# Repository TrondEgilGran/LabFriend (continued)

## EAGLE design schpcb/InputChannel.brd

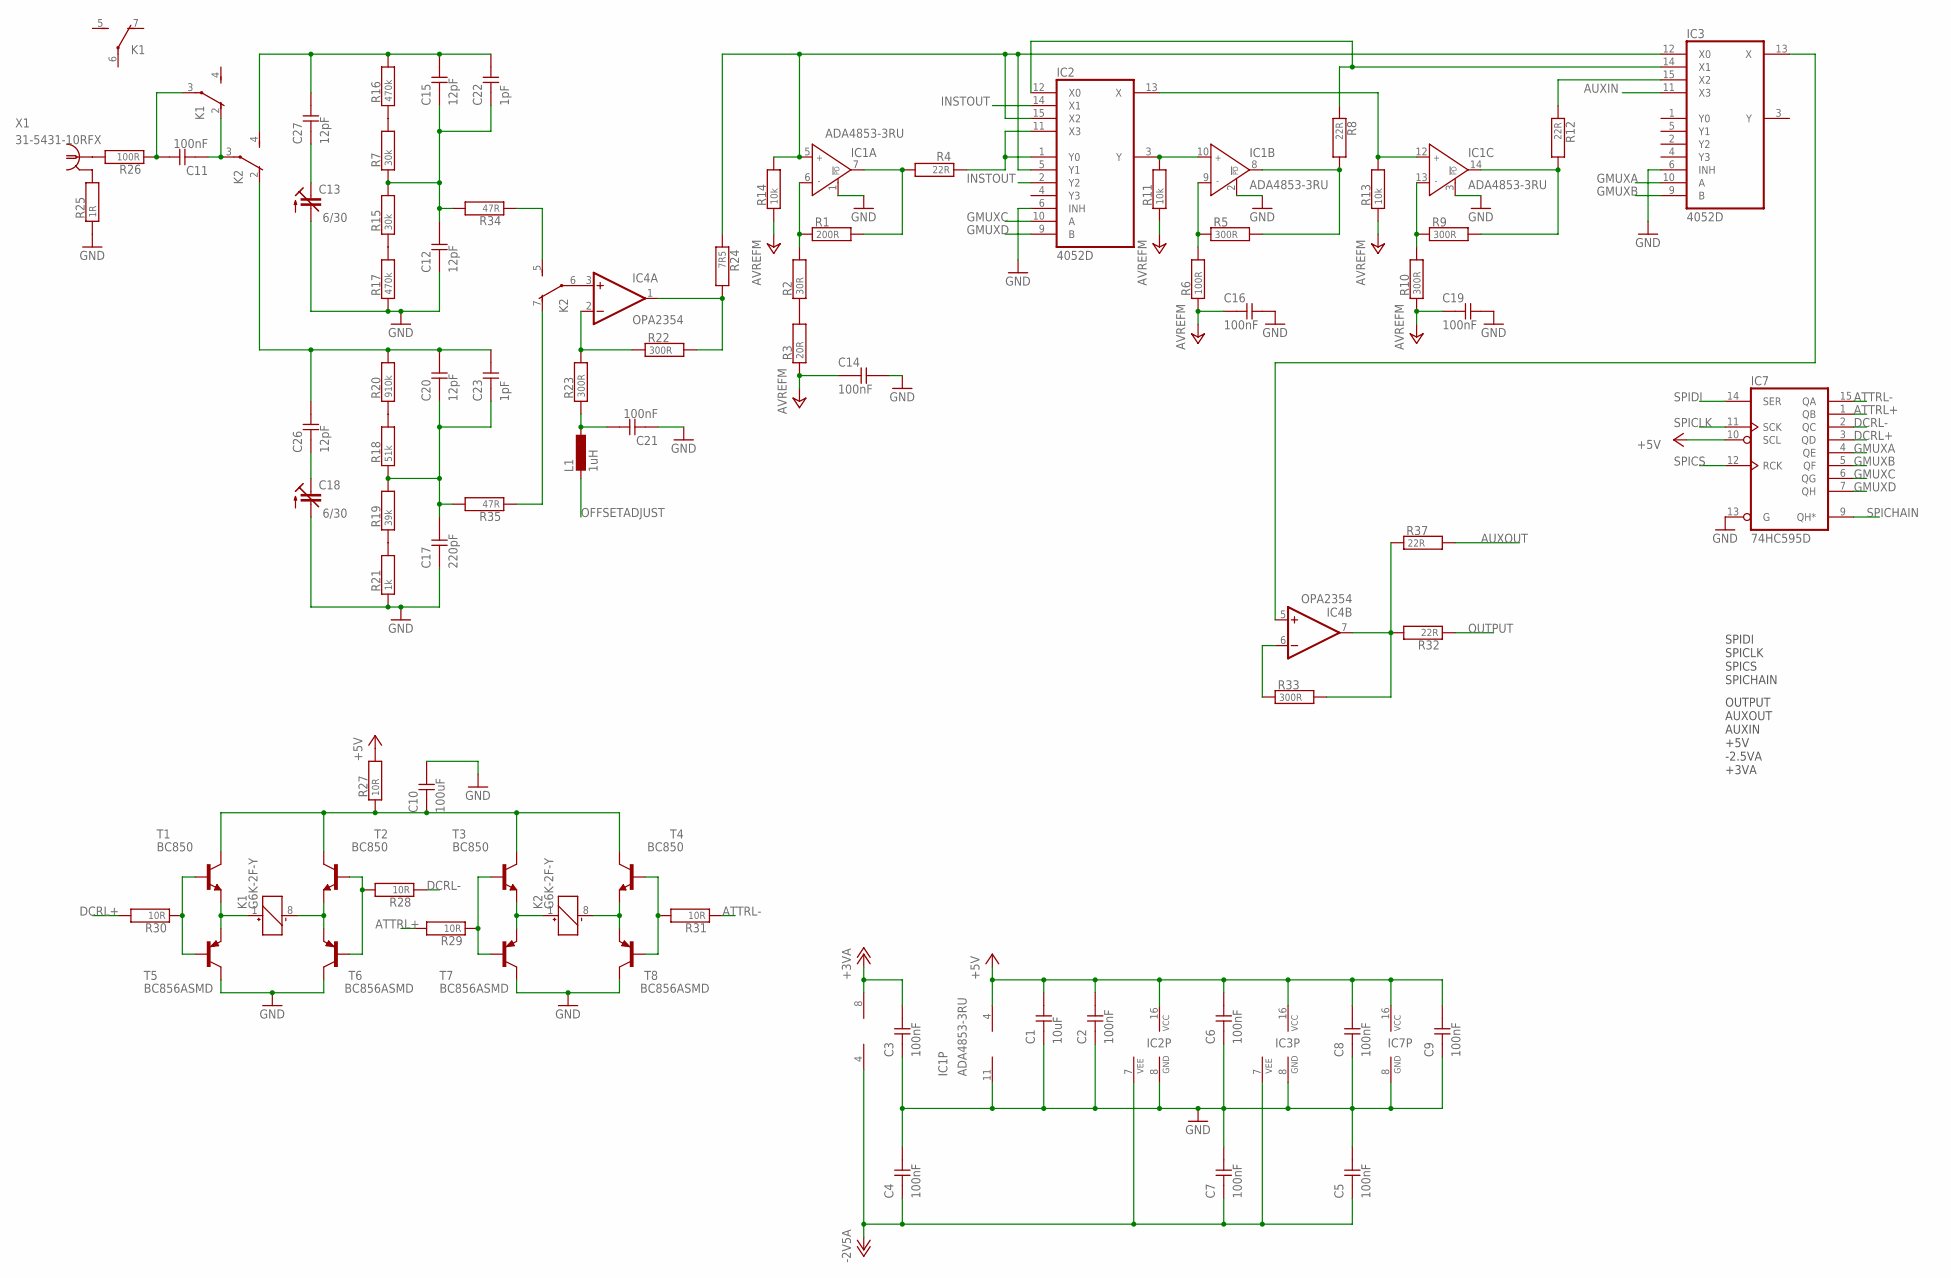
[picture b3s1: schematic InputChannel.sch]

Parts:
C1: 10uF; 0603
C2, C3, C5, C6, C7, C8, C9, C11: 100nF; 0603
C4, C14, C16, C19, C21: 100nF; 0402
C10: 100uF; 1206
C12, C15, C20, C26, C27: 12pF; 0603
C13, C18: 6/30; CTRIMTZBX4
C17: 220pF; 0603
C22, C23: 1pF; 0603
IC1: ADA4853-3RU; SO14
IC2, IC3: 4052D; SO16
IC4: OPA2354; MSOP08
IC7: 74HC595D; SO16
K1, K2: G6K-2F-Y
L1: 1uH; L3216C
R1: 200R; 0603
R2: 30R; 0603
R3: 20R; 0603
R4, R8, R12, R32, R37: 22R; 0603
R5, R9, R10, R22, R23, R33: 300R; 0603
R6, R26: 100R; 0603
R7, R15: 30k; 0603
R11, R13, R14: 10k; 0603
R16, R17: 470k; 0603
R18: 51k; 0603
R19: 39k; 0603
R20: 910k; 0603
R21: 1k; 0603
R24: 7R5; 0603
R25: 1R; 0603
R27, R28, R29, R30, R31: 10R; 0603
R34, R35: 47R; 0603
T1, T2, T3, T4: BC850; SOT23
T5, T6, T7, T8: BC856ASMD; SOT23-BEC
X1: 31-5431-10RFX; AMP_227161

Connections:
+3VA: C3.2, IC4.8 (V+)
+5V: C1.2, C2.2, C6.2, C8.2, C9.2, IC1.4 (V+), IC2.16 (VCC), IC3.16 (VCC), IC7.10 (SCL), IC7.16 (VCC), R27.2
-2V5A: C4.1, C5.1, C7.1, IC2.7 (VEE), IC3.7 (VEE), IC4.4 (V-)
ATTRL+: IC7.1 (QB), R29.2
ATTRL-: IC7.15 (QA), R31.1
AUXIN: IC3.11 (X3)
AUXOUT: R37.2
AVREFM: C14.1, C16.1, C19.1, R3.1, R6.1, R10.1, R11.1, R13.1, R14.1
DCRL+: IC7.3 (QD), R30.2
DCRL-: IC7.2 (QC), R28.1
GMUXA: IC3.10 (A), IC7.4 (QE)
GMUXB: IC3.9 (B), IC7.5 (QF)
GMUXC: IC2.10 (A), IC7.6 (QG)
GMUXD: IC2.9 (B), IC7.7 (QH)
GND: C1.1, C2.1, C3.1, C4.2, C5.2, C6.1, C7.2, C8.1, C9.1, C10.2, C12.1, C13.2 (A), C14.2, C16.2, C17.1, C18.2 (A), C19.2, C21.1, IC1.1 (!POWERDOWN), IC1.2 (!POWERDOWN), IC1.3 (!POWERDOWN), IC1.11 (V-), IC2.6 (INH), IC2.8 (GND), IC3.6 (INH), IC3.8 (GND), IC7.8 (GND), IC7.13 (G), R17.1, R21.1, R25.1, T5.C, T6.C, T7.C, T8.C
INSTOUT: IC2.2 (Y2), IC2.14 (X1)
unnamed: IC1.6 (IN-), R1.1, R2.2
unnamed: IC1.7 (OUT), R1.2, R4.2
unnamed: R2.1, R3.2
unnamed: C11.2, K1.3, R26.1
unnamed: IC1.9 (IN-), R5.1, R6.2
unnamed: IC2.1 (Y0), IC2.11 (X3), R4.1
unnamed: C11.1, K1.2 (O), K2.3
unnamed: IC2.12 (X0), IC3.14 (X1), R8.1
unnamed: IC1.12 (IN+), IC2.13 (X), R13.2
unnamed: IC1.5 (IN+), IC2.5 (Y1), IC2.15 (X2), IC3.12 (X0), R14.2, R24.1
unnamed: R7.2, R16.1
unnamed: IC1.13 (IN-), R9.1, R10.2
unnamed: IC1.14 (OUT), R9.2, R12.2
unnamed: IC3.15 (X2), R12.1
unnamed: IC1.8 (OUT), R5.2, R8.2
unnamed: C12.2, C15.1, C22.1, R7.1, R15.2, R34.2
unnamed: IC1.10 (IN+), IC2.3 (Y), R11.2
unnamed: R18.2, R20.1
unnamed: C17.2, C20.1, C23.1, R18.1, R19.2, R35.2
unnamed: R15.1, R17.2
unnamed: C15.2, C22.2, C27.2, K2.4 (S), R16.2
unnamed: R19.1, R21.2
unnamed: C20.2, C23.2, C26.2, K2.2 (O), R20.2
unnamed: R25.2, X1.2
unnamed: IC4.3 (+IN), K2.6
unnamed: C21.2, L1.1, R23.1
unnamed: IC4.2 (-IN), R22.1, R23.2
unnamed: IC4.1 (OUT), R22.2, R24.2
unnamed: R26.2, X1.1
unnamed: K2.5 (S), R34.1
unnamed: IC3.13 (X), IC4.5 (+IN)
unnamed: C10.1, R27.1, T1.3 (C), T2.3 (C), T3.3 (C), T4.3 (C)
unnamed: IC4.7 (OUT), R32.2, R33.2, R37.1
unnamed: K1.8 (-), T2.2 (E), T6.E
unnamed: K1.1 (+), T1.2 (E), T5.E
unnamed: R30.1, T1.1 (B), T5.B
unnamed: R28.2, T2.1 (B), T6.B
unnamed: K2.1 (+), T3.2 (E), T7.E
unnamed: K2.8 (-), T4.2 (E), T8.E
unnamed: IC4.6 (-IN), R33.1
unnamed: R29.1, T3.1 (B), T7.B
unnamed: R31.2, T4.1 (B), T8.B
unnamed: K2.7 (O), R35.1
unnamed: C18.1 (E), C26.1
unnamed: C13.1 (E), C27.1
OFFSETADJUST: L1.2
OUTPUT: R32.1
SPICHAIN: IC7.9 (QH*)
SPICLK: IC7.11 (SCK)
SPICS: IC7.12 (RCK)
SPIDI: IC7.14 (SER)

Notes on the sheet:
SPIDI SPICLK SPICS SPICHAIN
OUTPUT AUXOUT AUXIN +5V -2.5VA +3VA

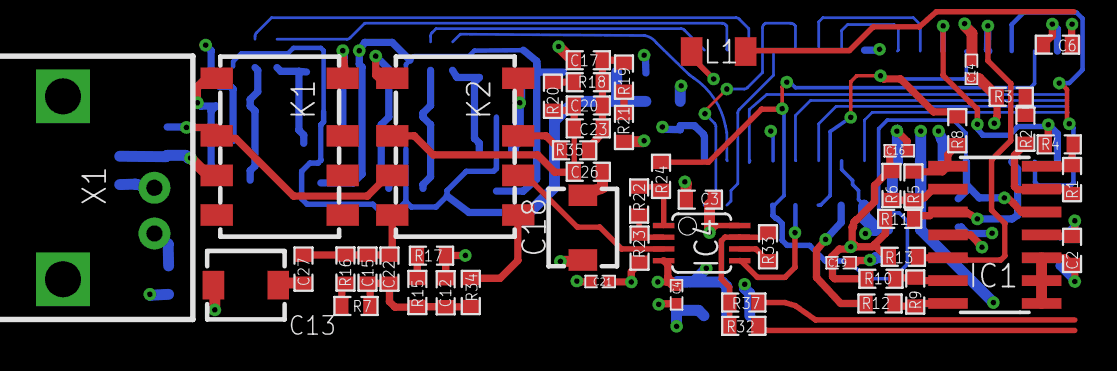
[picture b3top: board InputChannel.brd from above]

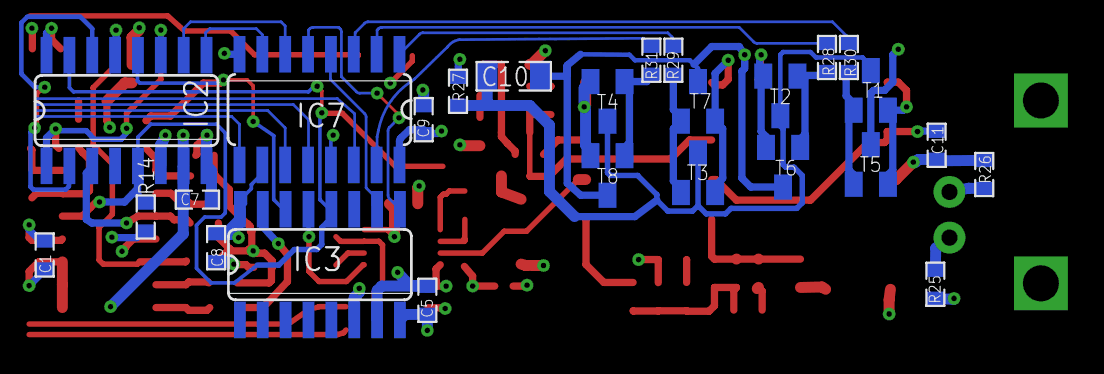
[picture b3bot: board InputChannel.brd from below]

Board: 4 copper layers, 78 parts (26 on the bottom side), 59 nets.

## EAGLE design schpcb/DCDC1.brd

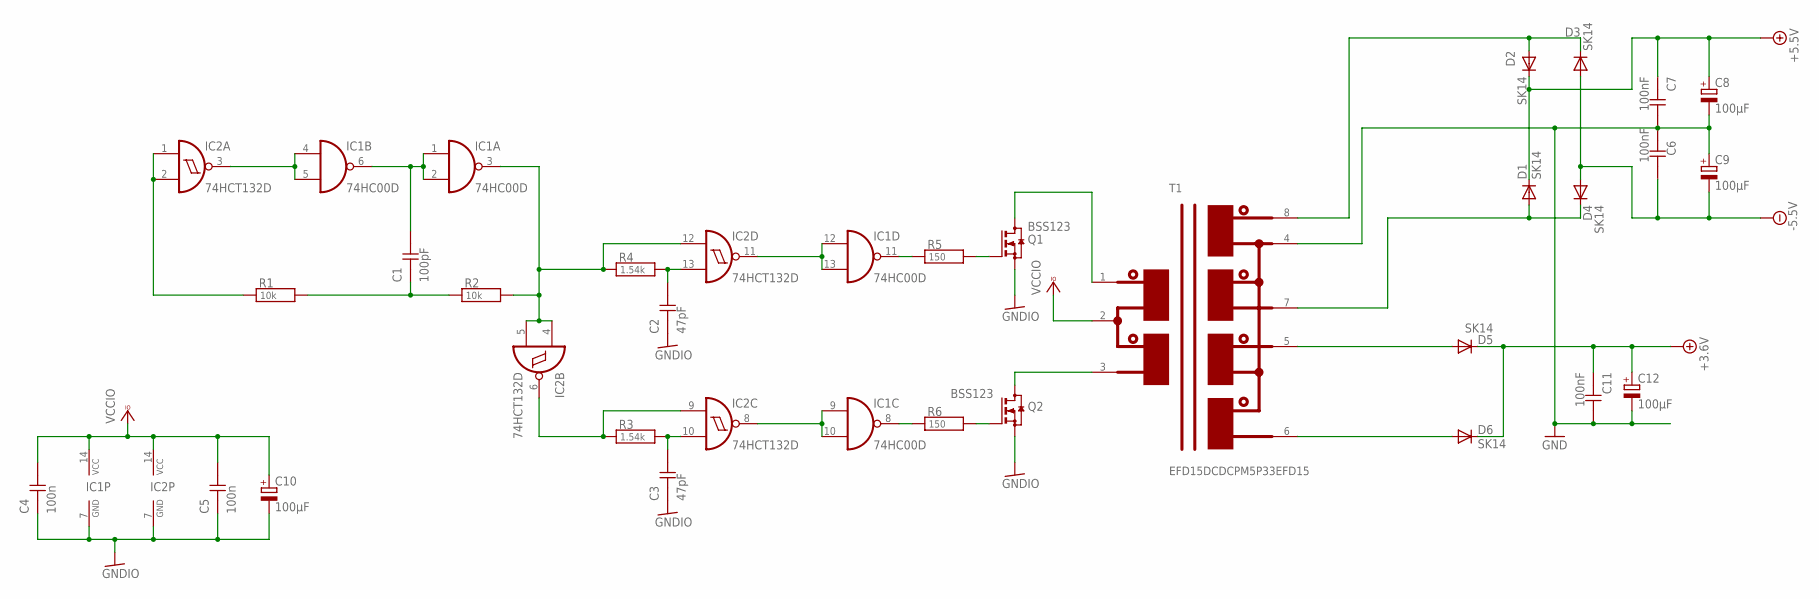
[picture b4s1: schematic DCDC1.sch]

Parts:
C1: 100pF; 0603
C2, C3: 47pF; 0603
C4, C5: 100n; 0603
C6, C7, C11: 100nF; 0603
C8, C9, C10, C12: 100µF; CT6032
D1, D2, D3, D4, D5, D6: SK14; DO214AC
IC1: 74HC00D; SO14
IC2: 74HCT132D; SO14
Q1, Q2: BSS123; SOT23
R1, R2: 10k; 0603
R3, R4: 1.54k; 0603
R5, R6: 150; 0603
T1: EFD15DCDCPM5P33EFD15; B66414-W1008-D1

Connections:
+3.6V: C11.1, C12.+, D5.C, D6.C
+5.5V: C7.1, C8.+, D1.C, D2.C
-5.5V: C6.2, C9.-, D3.A, D4.A
GND: C6.1, C7.2, C8.-, C9.+, C11.2, C12.-, T1.4 (SM)
GNDIO: C2.1, C3.1, C4.1, C5.1, C10.-, IC1.7 (GND), IC2.7 (GND), Q1.2 (S), Q2.2 (S)
unnamed: IC2.1 (I0), IC2.2 (I1), R1.1
unnamed: IC1.4 (I0), IC1.5 (I1), IC2.3 (O)
unnamed: C1.1, R1.2, R2.1
unnamed: C1.2, IC1.1 (I0), IC1.2 (I1), IC1.6 (O)
unnamed: IC1.3 (O), IC2.4 (I0), IC2.5 (I1), IC2.12 (I0), R2.2, R4.1
unnamed: IC1.12 (I0), IC1.13 (I1), IC2.11 (O)
unnamed: C2.2, IC2.13 (I1), R4.2
unnamed: IC2.6 (O), IC2.9 (I0), R3.1
unnamed: C3.2, IC2.10 (I1), R3.2
unnamed: IC1.9 (I0), IC1.10 (I1), IC2.8 (O)
unnamed: IC1.11 (O), R5.1
unnamed: IC1.8 (O), R6.1
unnamed: Q2.1 (G), R6.2
unnamed: D5.A, T1.5 (S2P)
unnamed: Q1.1 (G), R5.2
unnamed: Q1.3 (D), T1.1 (P1P)
unnamed: D1.A, D4.C, T1.7 (S1N)
unnamed: D2.A, D3.C, T1.8 (S1P)
unnamed: Q2.3 (D), T1.3 (P1N)
unnamed: D6.A, T1.6 (S2N)
VCCIO: C4.2, C5.2, C10.+, IC1.14 (VCC), IC2.14 (VCC), T1.2 (P1M)

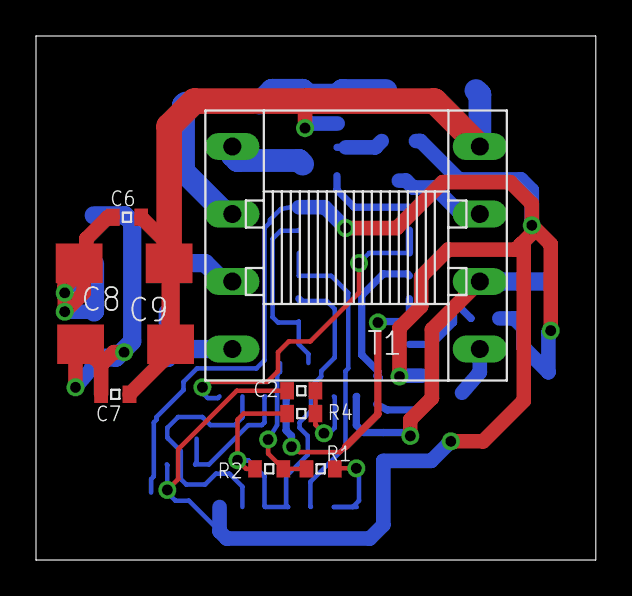
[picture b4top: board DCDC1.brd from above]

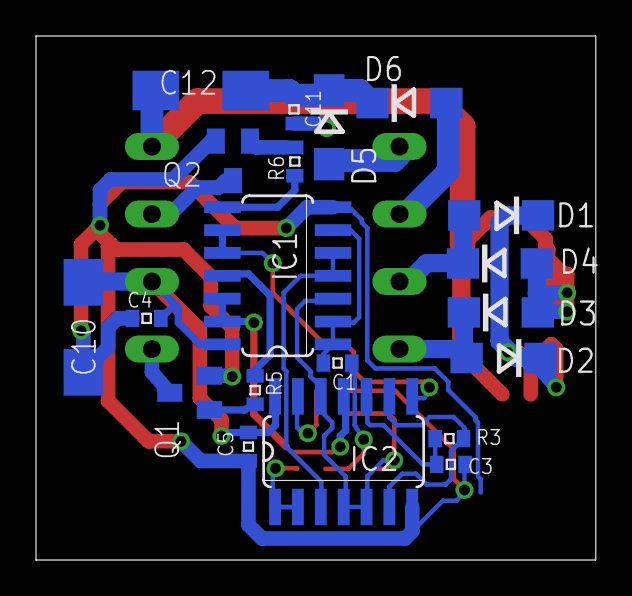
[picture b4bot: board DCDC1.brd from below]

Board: 2 copper layers, 31.1 x 29.1 mm, 29 parts (20 on the bottom side), 26 nets.

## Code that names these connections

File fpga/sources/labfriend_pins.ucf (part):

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
###### I2S Pin Config ####################
# I2SSCLK
NET "I2SSCLK" LOC = P16;
NET "I2SSCLK" IOSTANDARD = LVCMOS33;
NET "I2SSCLK" OUT_TERM = UNTUNED_50;
#I2SDATAIN
NET "I2SDATAIN" LOC = M16;
NET "I2SDATAIN" IOSTANDARD = LVCMOS33;
NET "I2SDATAOUT" OUT_TERM = UNTUNED_50;
#I2SDATAOUT
NET "I2SDATAOUT" LOC = N14;
NET "I2SDATAOUT" IOSTANDARD = LVCMOS33;
#I2SBCK
NET "I2SBCK" LOC = N16;
NET "I2SBCK" IOSTANDARD = LVCMOS33;
NET "I2SBCK" OUT_TERM = UNTUNED_50;
#I2SLRCK
NET "I2SLRCK" LOC = P15;
NET "I2SLRCK" IOSTANDARD = LVCMOS33;
NET "I2SLRCK" OUT_TERM = UNTUNED_50;

##### MasterClock #######################
# MSTCLK
NET "MSTCLK" LOC = B10;
NET "MSTCLK" IOSTANDARD = LVCMOS33;

#### GPSPI/ SCOPE SPI CONNECTION ########
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
######### PWM outputs ########################
#
NET "PWMOFFS0" LOC = C10;
NET "PWMOFFS0" IOSTANDARD = LVCMOS33;
NET "PWMOFFS1" LOC = C11;
NET "PWMOFFS1" IOSTANDARD = LVCMOS33;
NET "PWMEXVO" LOC = D11;
NET "PWMEXVO" IOSTANDARD = LVCMOS33;
NET "PWMLAVIO" LOC = D12;
NET "PWMLAVIO" IOSTANDARD = LVCMOS33;
NET "PWMLA" LOC = E12;
NET "PWMLA" IOSTANDARD = LVCMOS33;
NET "LADVREF" LOC = N6;
NET "LADVREF" IOSTANDARD = LVCMOS33;

### FLASH Memory ########################
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
#### ANALG SELECT #####################
# Select commponent Measurement or Audio
NET "CMP_MEAS_SEL" LOC = R16;
NET "CMP_MEAS_SEL" IOSTANDARD = LVCMOS33;
# Component measure range
NET "CMPMEAS_EN" LOC = N12;
NET "CMPMEAS_EN" IOSTANDARD = LVCMOS33;
NET "CMPMEAS_A" LOC = R12;
NET "CMPMEAS_A" IOSTANDARD = LVCMOS33;
NET "CMPMEAS_B" LOC = M13;
NET "CMPMEAS_B" IOSTANDARD = LVCMOS33;

### Digital IO + 1 CH AWG #############
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NET "ADA[6]" IOSTANDARD = LVCMOS33;
NET "ADA[7]" LOC = B15;
NET "ADA[7]" IOSTANDARD = LVCMOS33;
NET "ADAC" LOC = F15;
NET "ADAC" IOSTANDARD = LVCMOS33;
NET "ADAC" OUT_TERM = UNTUNED_50;
NET "ADAP" LOC = F16;
NET "ADAP" IOSTANDARD = LVCMOS33;
# ADB
NET "ADB[0]" LOC = K14;
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NET "ADB[6]" IOSTANDARD = LVCMOS33;
NET "ADB[7]" LOC = F14;
NET "ADB[7]" IOSTANDARD = LVCMOS33;
NET "ADBC" LOC = L16;
NET "ADBC" IOSTANDARD = LVCMOS33;
NET "ADBC" OUT_TERM = UNTUNED_50;

##### HF DAC Connections #######################
##
NET "HFDAC_DI" LOC = L13;
NET "HFDAC_DI" IOSTANDARD = LVCMOS33;
NET "HFDAC_DI" OUT_TERM = UNTUNED_50;
NET "HFDAC_CS" LOC = J13;
NET "HFDAC_CS" IOSTANDARD = LVCMOS33;
NET "HFDAC_CS" OUT_TERM = UNTUNED_50;
NET "HFDAC_CLK" LOC = F13;
NET "HFDAC_CLK" IOSTANDARD = LVCMOS33;
NET "HFDAC_CLK" OUT_TERM = UNTUNED_50;
#NET "HFDAC_CLK" CLOCK_DEDICATED_ROUTE = FALSE;

#### LF Control SPI ##################################
# Audio CODEC and DC ADC SPI 
NET "AU_CSN" LOC = T13;
NET "AU_CSN" IOSTANDARD = LVCMOS33;
NET "AU_CSN" OUT_TERM = UNTUNED_50;
NET "AU_CCLK" LOC = T14;
NET "AU_CCLK" IOSTANDARD = LVCMOS33;
NET "AU_CCLK" OUT_TERM = UNTUNED_50;
NET "AU_CDTI" LOC = T15;
NET "AU_CDTI" IOSTANDARD = LVCMOS33;
NET "AU_CDTI" OUT_TERM = UNTUNED_50;
NET "DC_DOUT" LOC = T12;
NET "DC_DOUT" IOSTANDARD = LVCMOS33;
NET "DC_CS" LOC = M14;
NET "DC_CS" IOSTANDARD = LVCMOS33;
NET "DC_CS" OUT_TERM = UNTUNED_50;
# Audio Control
NET "AUPDN" LOC = R15;
NET "AUPDN" IOSTANDARD = LVCMOS33;
NET "AUPDN" OUT_TERM = UNTUNED_50;
NET "AU_OVFR" LOC = M15;
NET "AU_OVFR" IOSTANDARD = LVCMOS33;
NET "AU_OVFL" LOC = R14;
NET "AU_OVFL" IOSTANDARD = LVCMOS33;

############################################################################
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
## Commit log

2015-07-10 added new datasheet
2015-07-10 Finished first outcast for inputchannel
2015-07-13 added analog switch datasheet
2015-08-07 current state
2015-08-07 added datasheeets
2015-08-18 added new datasheets
2015-08-18 Pre release checkin
2015-08-24 Final oreder prototype
2015-08-24 Final proto version
2015-09-11 added software and FPGA paths
2015-09-14 new fpga sources
2015-09-14 added library files
2015-09-14 Added ddr
2015-09-14 lalal
2015-09-24 Some changes
2015-09-24 Started adding chnge comments
2015-09-24 Small chnages
2015-09-24 DDR3L ram used in design datasheet
2015-09-28 added pwm
2015-09-28 Addew pwm to main
2015-09-28 aded last pwm pin
2015-09-29 fixed
2015-09-30 Added xilinx spartan 6 hdl guide
2015-09-30 changed to all logic instead of ulogic
2015-09-30 changed from ulogic to logic
2015-10-07 Added changes
2015-10-07 Fixed errors in FPGA code
2015-10-12 working one channel
2015-10-14 Chnaged to one RAM channel
2015-10-14 Added single ram channel usage
2015-10-14 TEst
2015-10-16 fixed some errors
2015-10-16 fixit
2015-10-19 Almost working
2015-10-20 lala
2015-10-20 Fixed problem with read synch
2015-10-20 trigger readded
2015-10-27 Tried to fix start address issues
2015-10-28 reoundcount problems may be fixed.
2015-10-29 Changed to correct reoundcounting of read counter
2015-10-30 added ddr3 sources from core generator to project
2015-11-11 Added QCustomplot to gui
2015-11-12 added fft real library
2015-11-12 added gui program based on superscope
2015-11-12 added copy of i2c dac from superscope, renamed to dcio, should control pwm + DC ADC
2015-11-16 added spi interface, currently just copy of 74595
2015-11-19 Added spi code to make Audio DAC/ADC work
2015-11-19 Test Code for audio DACADC
2015-11-19 fixed library
2015-11-24 Added HS DAC code, tested and working!!!!!!!!!!
2015-11-24 transformer design
2015-11-24 latest changes
2015-11-24 added trafo doc
2015-11-26 added ftdi chip eeprom programming and udev rules
2015-11-26 "made opening of ftdi device device specific to avoid trying to use other devices"
2015-11-30 Added latest test of full speed, should redo the system
2015-12-01 Working at 200MSP, still roundcounter problem should be fixed
2016-02-21 Changed to new method for counting ram addresses
2016-03-13 Latest changes for
2016-03-20 :q!
    :w
2016-03-29 added missing files
2016-04-27 Changed to fixed 4x clock for hs adc to get correct clock constraints
2016-04-30 working partially still much left but this is a starting point for new gen
2016-04-30 Working variable buffersize and added reset.
2016-09-25 removed many bugs now working with triggering, remaining more updates of fpga code for speed
2017-02-03 added bow drawings
2017-02-03 added top and bottom
2017-02-17 added awg and dwg functions, fixed byte order inside was wrong, four and four bits was in the wrong order
2017-02-19 added adc input registgers to iob
2017-02-19 cleaned up
2017-02-24 added hw bug list
2017-02-24 many improovments and bugfixes and added features
2017-02-24 added calibration and test structure and unfinished file for SN1
2017-02-25 Tried to increase draw speed
2017-03-01 fixed speed issues and improved calibration
2017-03-06 Fixed scope timeo offset and triggering
2017-03-08 push correct start trigg value on auto trigging
2017-03-08 corrected autorun and added compile parameter for libmpsse
2017-03-08 added file for programming spi flash trough xc3sprog
2017-03-08 added my own changes to xc3sprog to make it work with my programmer, this tool is faster to use and takes much less space than impact
2017-03-09 added directories for labfriend accessories
2017-03-09 added micamp
2017-03-09 started documentation
2017-03-11 corrected to support 96khz
2017-03-11 audio fixes --not finished
2017-03-17 added mls, still work in progress
2017-03-17 added sync on fpga and fix some things on audiomeaskit
2017-03-20 chages to make plot type better and improved mls support
2017-03-23 added fft impulse response button and set micamp button
2017-03-23 added zeero level swtich
2017-04-03 fixed memory errors not detected under centos
